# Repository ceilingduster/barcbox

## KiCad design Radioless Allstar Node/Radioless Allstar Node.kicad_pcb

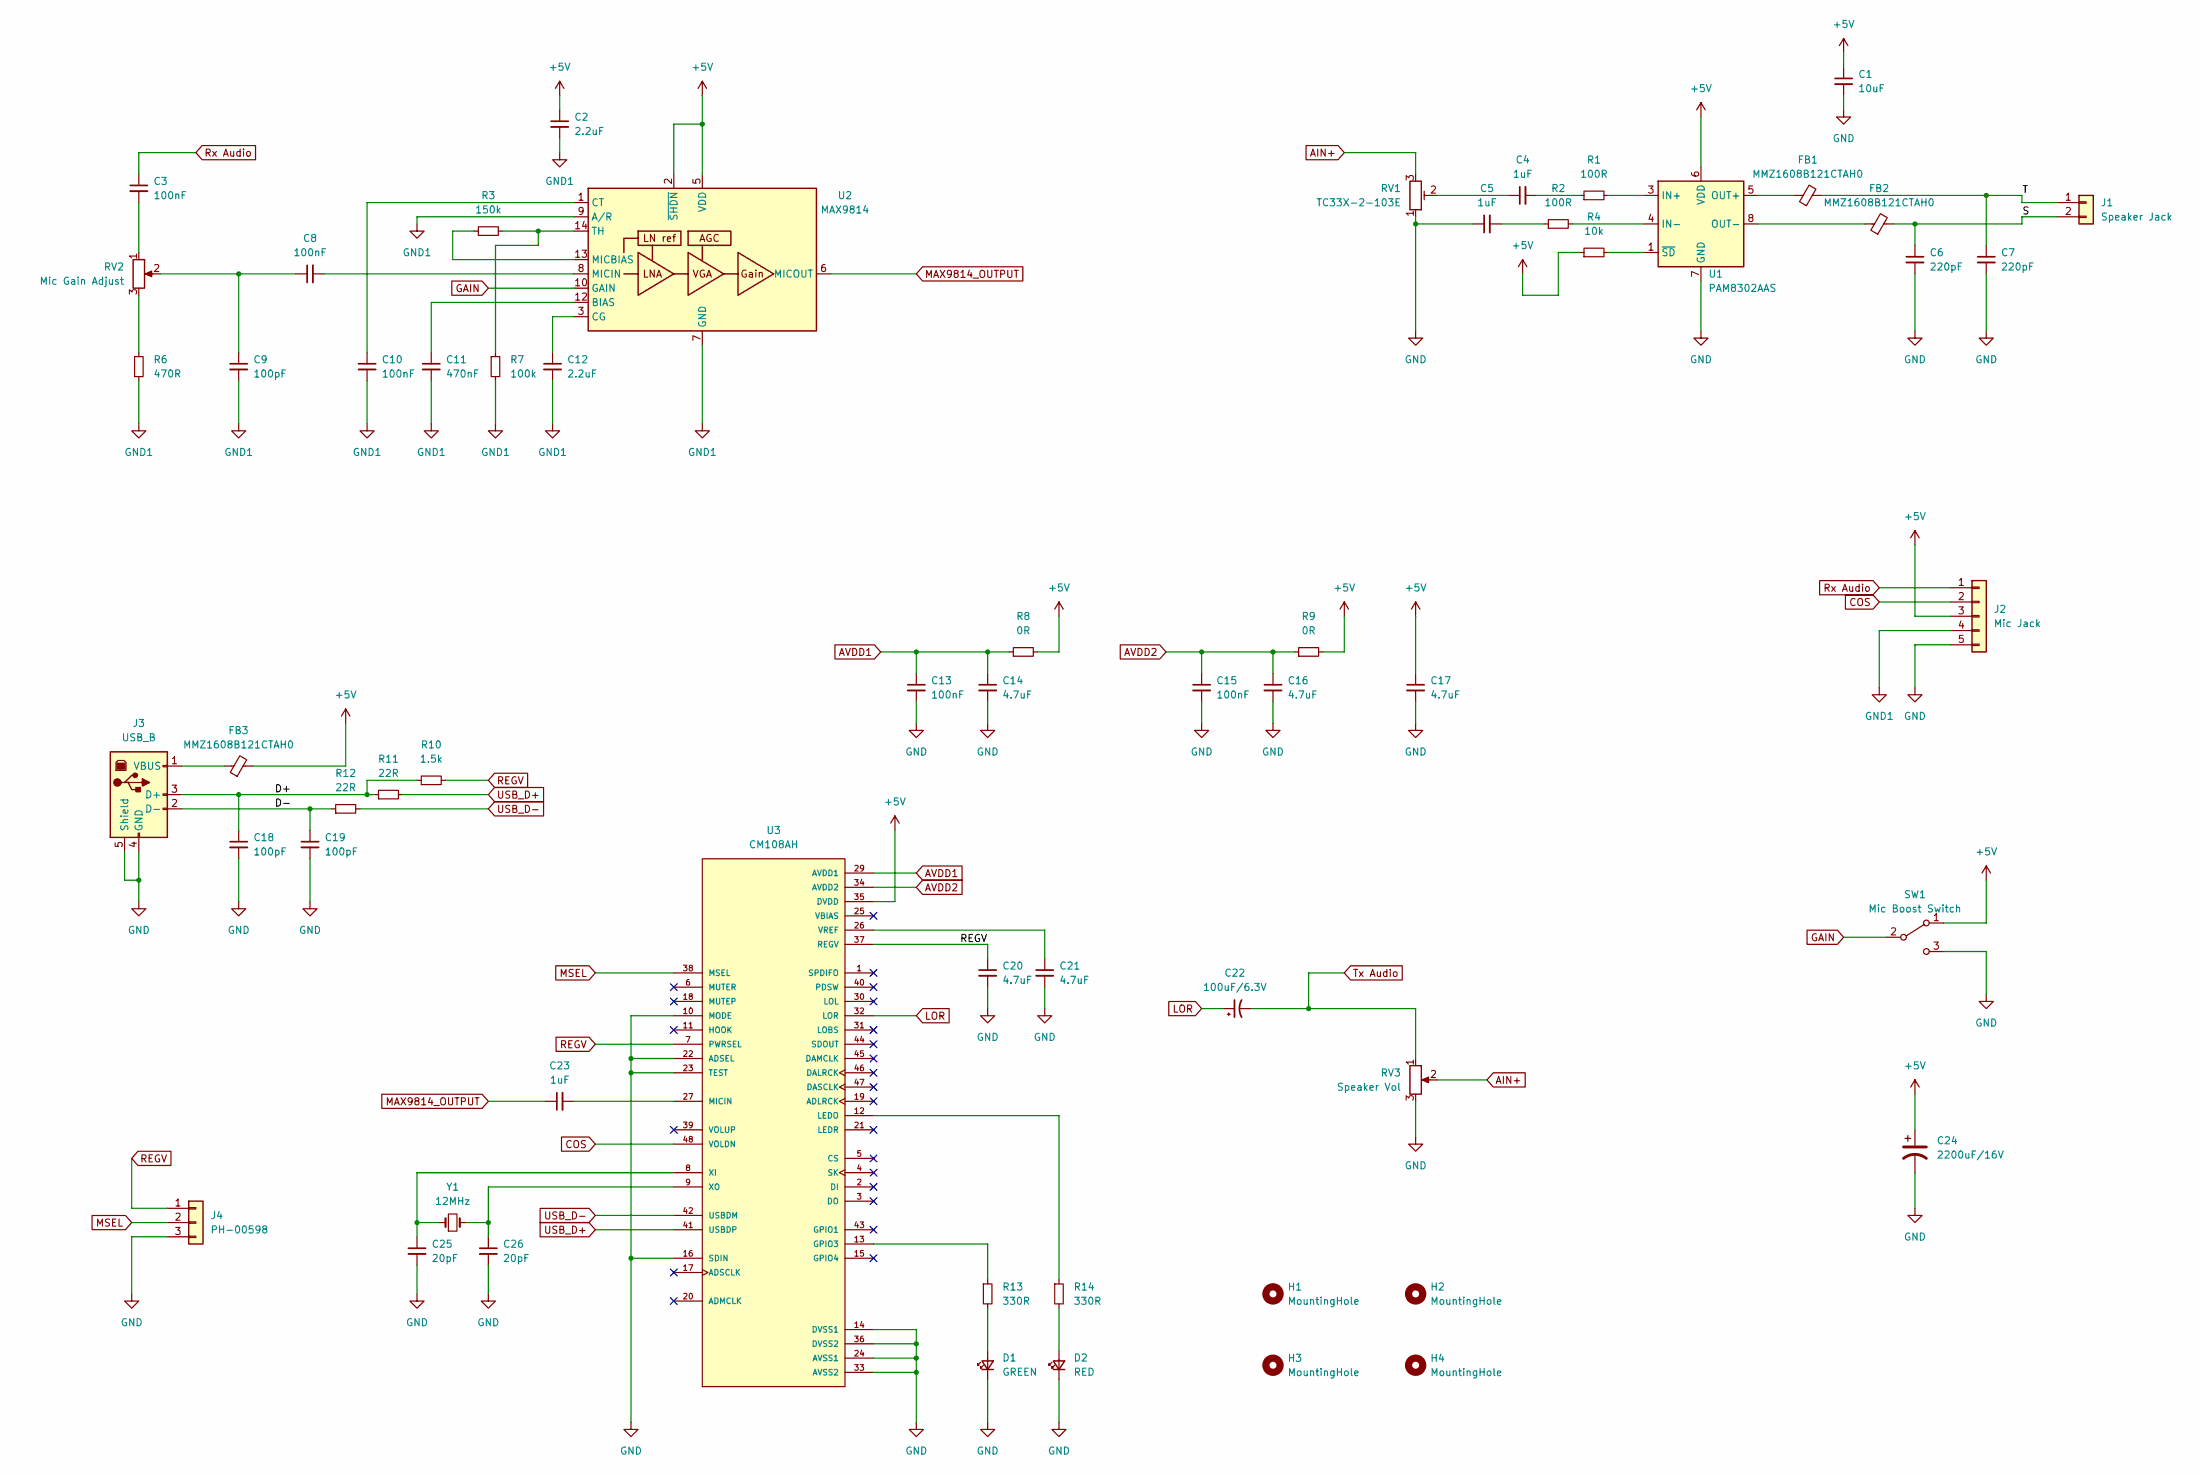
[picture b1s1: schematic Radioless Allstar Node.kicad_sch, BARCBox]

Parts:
C1: 10uF; C_0603_1608Metric; LCSC Part # C19702
C2, C12: 2.2uF; C_0603_1608Metric; LCSC Part # C23630
C3, C8, C10, C13, C15: 100nF; C_0603_1608Metric; LCSC Part # C14663
C4, C5, C23: 1uF; C_0603_1608Metric; LCSC Part # C15849
C6, C7: 220pF; C_0603_1608Metric; LCSC Part # C1603
C9, C18, C19: 100pF; C_0603_1608Metric; LCSC Part # C14858
C11: 470nF; C_0603_1608Metric; LCSC Part # C1623
C14, C16, C17, C20, C21: 4.7uF; C_0603_1608Metric; LCSC Part # C19666
C22: 100uF/6.3V; C_1206_3216Metric; LCSC Part # C15008
C24: 2200uF/16V; C_Radial_D10.0mm_H20.0mm_P5.00mm; LCSC Part # C697579
C25, C26: 20pF; C_0603_1608Metric; LCSC Part # C1648
D1: GREEN; LED_D3.0mm; LCSC Part # C99761
D2: RED; LED_0603_1608Metric; LCSC Part # C2286
FB1, FB2, FB3: MMZ1608B121CTAH0; L_0603_1608Metric; LCSC Part # C275436
H1, H2, H3, H4: MountingHole; MountingHole_3.2mm_M3_ISO14580
J1: Speaker Jack
J2: Mic Jack
J3: USB_B; USB_B_OST_USB-B1HSxx_Horizontal; LCSC Part # C46393
J4: PH-00598; PinHeader_1x03_P2.54mm_Vertical; LCSC Part # C2999447
R1, R2: 100R; R_0603_1608Metric; LCSC Part # C22775
R3: 150k; R_0603_1608Metric; LCSC Part # C22807
R4: 10k; R_0603_1608Metric; LCSC Part # C25804
R6: 470R; R_0603_1608Metric; LCSC Part # C23179
R7: 100k; R_0603_1608Metric; LCSC Part # C25803
R8, R9: 0R; R_0603_1608Metric; LCSC Part # C21189
R10: 1.5k; R_0603_1608Metric; LCSC Part # C22843
R11, R12: 22R; R_0603_1608Metric; LCSC Part # C23345
R13, R14: 330R; R_0603_1608Metric; LCSC Part # C23138
RV1: TC33X-2-103E; Potentiometer_Bourns_TC33X_Vertical; LCSC Part # C719176
RV2: Mic Gain Adjust
RV3: Speaker Vol
SW1: Mic Boost Switch
U1: PAM8302AAS; MSOP-8_3x3mm_P0.65mm; LCSC Part # C113367
U2: MAX9814; DFN-14-1EP_3x3mm_P0.4mm_EP1.78x2.35mm; LCSC Part # C41714
U3: CM108AH; LCSC Part # C371346
Y1: 12MHz; Crystal_SMD_HC49-SD; LCSC Part # C111117

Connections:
+5V: C1.1, C2.1, C17.1, C24.1, FB3.2, J2.3, R4.1, R8.2, R9.2, SW1.1 (A), U1.6 (VDD), U2.2 (~SHDN), U2.5 (VDD), U3.35 (DVDD)
/D+: C18.1, J3.3 (D+), R10.1, R11.1
/D-: C19.1, J3.2 (D-), R12.1
/S: C6.1, FB2.2, J1.2
/T: C7.1, FB1.2, J1.1
AIN+: RV1.3, RV3.2
AVDD1: C13.1, C14.1, R8.1, U3.29 (AVDD1)
AVDD2: C15.1, C16.1, R9.1, U3.34 (AVDD2)
COS: J2.2, U3.48 (VOLDN)
GAIN: SW1.2 (B), U2.10 (GAIN)
GND: C1.2, C5.1, C6.2, C7.2, C13.2, C14.2, C15.2, C16.2, C17.2, C18.2, C19.2, C20.2, C21.2, C24.2, C25.2, C26.2, D1.1 (K), D2.1 (K), J2.5, J3.4 (GND), J3.5 (Shield), J4.3, RV1.1, RV3.3, SW1.3 (C), U1.7 (GND), U3.10 (MODE), U3.14 (DVSS1), U3.16 (SDIN), U3.22 (ADSEL), U3.23 (TEST), U3.24 (AVSS1), U3.33 (AVSS2), U3.36 (DVSS2)
GND1: C2.2, C9.2, C10.2, C11.2, C12.2, J2.4, R6.2, R7.2, U2.4 (GND), U2.7 (GND), U2.9 (A/R), U2.11 (GND), U2.15 (GND)
LOR: C22.1, U3.32 (LOR)
MAX9814_OUTPUT: C23.1, U2.6 (MICOUT)
MSEL: J4.2, U3.38 (MSEL)
unnamed: C3.2, RV2.1
unnamed: C4.1, RV1.2
unnamed: C4.2, R1.1
unnamed: C5.2, R2.1
unnamed: C8.1, C9.1, RV2.2
unnamed: C8.2, U2.8 (MICIN)
unnamed: C10.1, U2.1 (CT)
unnamed: C11.1, U2.12 (BIAS)
unnamed: C12.1, U2.3 (CG)
unnamed: C21.1, U3.26 (VREF)
unnamed: C23.2, U3.27 (MICIN)
unnamed: C25.1, U3.8 (XI), Y1.1
unnamed: C26.1, U3.9 (XO), Y1.2
unnamed: D1.2 (A), R13.2
unnamed: D2.2 (A), R14.2
unnamed: FB1.1, U1.5 (OUT+)
unnamed: FB2.1, U1.8 (OUT-)
unnamed: FB3.1, J3.1 (VBUS)
unnamed: R1.2, U1.3 (IN+)
unnamed: R2.2, U1.4 (IN-)
unnamed: R3.1, U2.13 (MICBIAS)
unnamed: R3.2, R7.1, U2.14 (TH)
unnamed: R4.2, U1.1 (~SD)
unnamed: R6.1, RV2.3
unnamed: R13.1, U3.13 (GPIO3)
unnamed: R14.1, U3.12 (LEDO)
REGV: C20.1, J4.1, R10.2, U3.7 (PWRSEL), U3.37 (REGV)
Rx Audio: C3.1, J2.1
Tx Audio: C22.2, RV3.1
USB_D+: R11.2, U3.41 (USBDP)
USB_D-: R12.2, U3.42 (USBDM)

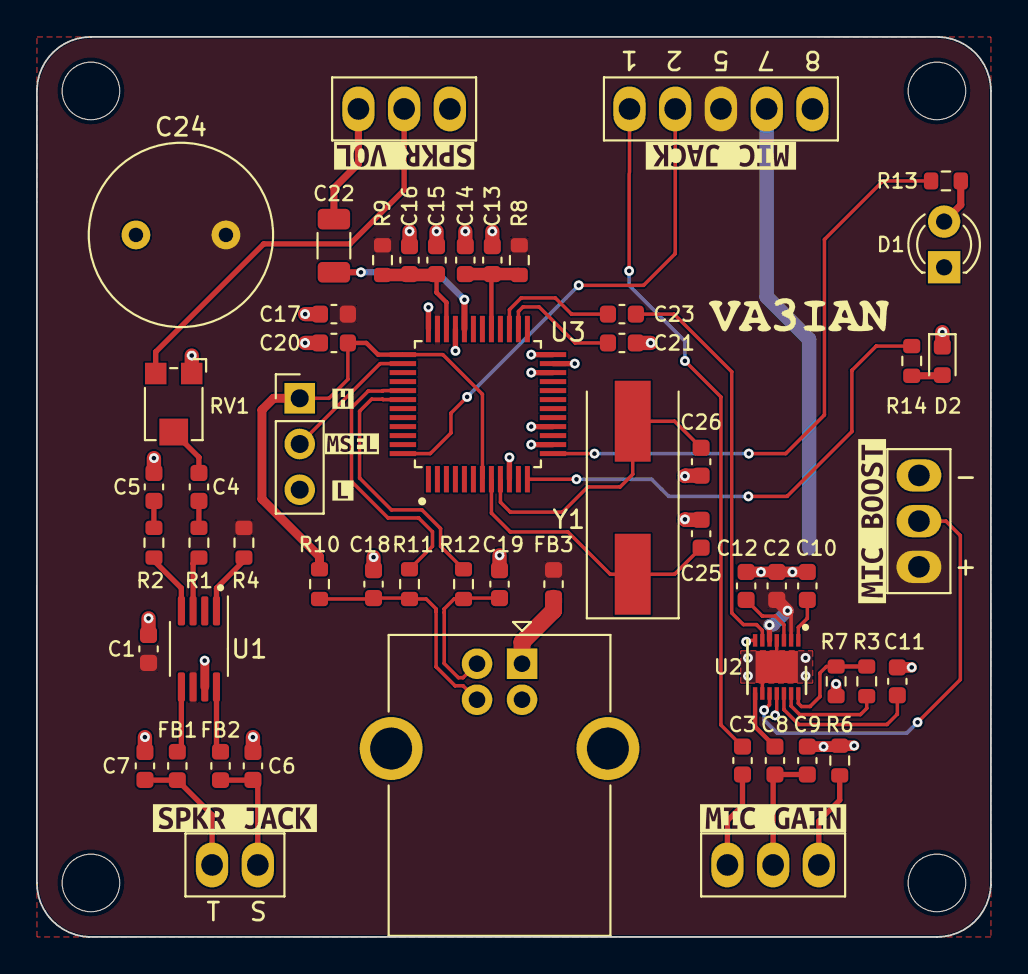
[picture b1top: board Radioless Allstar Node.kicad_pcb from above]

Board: 2 copper layers, 53.0 x 50.0 mm, 68 parts (0 on the bottom side), 46 nets.

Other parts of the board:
kibuzzard-6481EDD5: G***; kibuzzard-6481EDD5
kibuzzard-6481EDF2: G***; kibuzzard-6481EDF2
kibuzzard-6481EE0B: G***; kibuzzard-6481EE0B
kibuzzard-6481F34A: G***; kibuzzard-6481F34A
kibuzzard-6481F543: G***; kibuzzard-6481F543
kibuzzard-648228C2: G***; kibuzzard-648228C2
kibuzzard-6482294B: G***; kibuzzard-6482294B
kibuzzard-6482295C: G***; kibuzzard-6482295C

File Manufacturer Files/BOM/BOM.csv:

Comment,Designator,Footprint,JLCPCB Part #
10uF,    C1,Capacitor_SMD:C_0603_1608Metric,C19702
220pF,"    C6, C7",Capacitor_SMD:C_0603_1608Metric,C1603
100nF,"    C3, C8, C10, C13, C15",Capacitor_SMD:C_0603_1608Metric,C14663
470nF,    C11,Capacitor_SMD:C_0603_1608Metric,C1623
2.2uF,"    C2, C12",Capacitor_SMD:C_0603_1608Metric,C23630
100pF,"    C9, C18, C19",Capacitor_SMD:C_0603_1608Metric,C14858
4.7uF,"    C14, C16, C17, C20, C21",Capacitor_SMD:C_0603_1608Metric,C19666
100uF/6.3V,    C22,Capacitor_SMD:C_1206_3216Metric,C15008
1uF,"    C4, C5, C23",Capacitor_SMD:C_0603_1608Metric,C15849
2200uF/16V,    C24,Capacitor_THT:C_Radial_D10.0mm_H20.0mm_P5.00mm,C697579
20pF,"    C25, C26",Capacitor_SMD:C_0603_1608Metric,C1648
GREEN,    D1,LED_THT:LED_D3.0mm,C99761
RED,    D2,LED_SMD:LED_0603_1608Metric,C2286
MMZ1608B121CTAH0,"    FB1, FB2, FB3",Inductor_SMD:L_0603_1608Metric,C275436
USB_B,    J3,Connector_USB:USB_B_OST_USB-B1HSxx_Horizontal,C46393
PH-00598,    J4,Connector_PinHeader_2.54mm:PinHeader_1x03_P2.54mm_Vertical,C2999447
100R,"    R1, R2",Resistor_SMD:R_0603_1608Metric,C22775
150k,    R3,Resistor_SMD:R_0603_1608Metric,C22807
10k,    R4,Resistor_SMD:R_0603_1608Metric,C25804
470R,    R6,Resistor_SMD:R_0603_1608Metric,C23179
100k,    R7,Resistor_SMD:R_0603_1608Metric,C25803
0R,"    R8, R9",Resistor_SMD:R_0603_1608Metric,C21189
1.5k,    R10,Resistor_SMD:R_0603_1608Metric,C22843
22R,"    R11, R12",Resistor_SMD:R_0603_1608Metric,C23345
330R,"    R13, R14",Resistor_SMD:R_0603_1608Metric,C23138
TC33X-2-103E,    RV1,Potentiometer_SMD:Potentiometer_Bourns_TC33X_Vertical,C719176
PAM8302AAS,    U1,Package_SO:MSOP-8_3x3mm_P0.65mm,C113367
MAX9814,    U2,Package_DFN_QFN:DFN-14-1EP_3x3mm_P0.4mm_EP1.78x2.35mm,C41714
CM108AH,    U3,LQFP-48(7x7),C371346
12MHz,    Y1,Crystal:Crystal_SMD_HC49-SD,C111117
